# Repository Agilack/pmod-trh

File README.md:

PMOD Temperature and Humidity
=============================

This PMOD use an Si7021 sensor for temperature and humidity measurement.

**WARNING** Because of a bad choice into io assignment, it is not possible to
use UART TX/RX pins on PMOD connector (conflict for SERCOM0 already used for
I2C interface). Fortunately the TX/RX signals of SERCOM1 can be connected to
the pins named CTS/RTS of PMOD. This is an hardware bug that will be fix on
next version.

CAD source
----------

This board has been designed using KiCad EDA (version 6). All sources files
(schematics, routing, ...) are available into the `prj-kicad` folder.

This project is OpenHardware. You can re-use this design under terms of the
Creative Commons  ShareAlike license (CC-by-SA). See [LICENSE.md](LICENSE.md).

<table>
<tr>
<td></td>
<td></td>
</tr>
<tr>
<td>Fig1: Preview of the KiCad schematics (rev2)</td>
<td>Fig2: Preview of the KiCad routing (rev2)</td>
</tr>
</table>

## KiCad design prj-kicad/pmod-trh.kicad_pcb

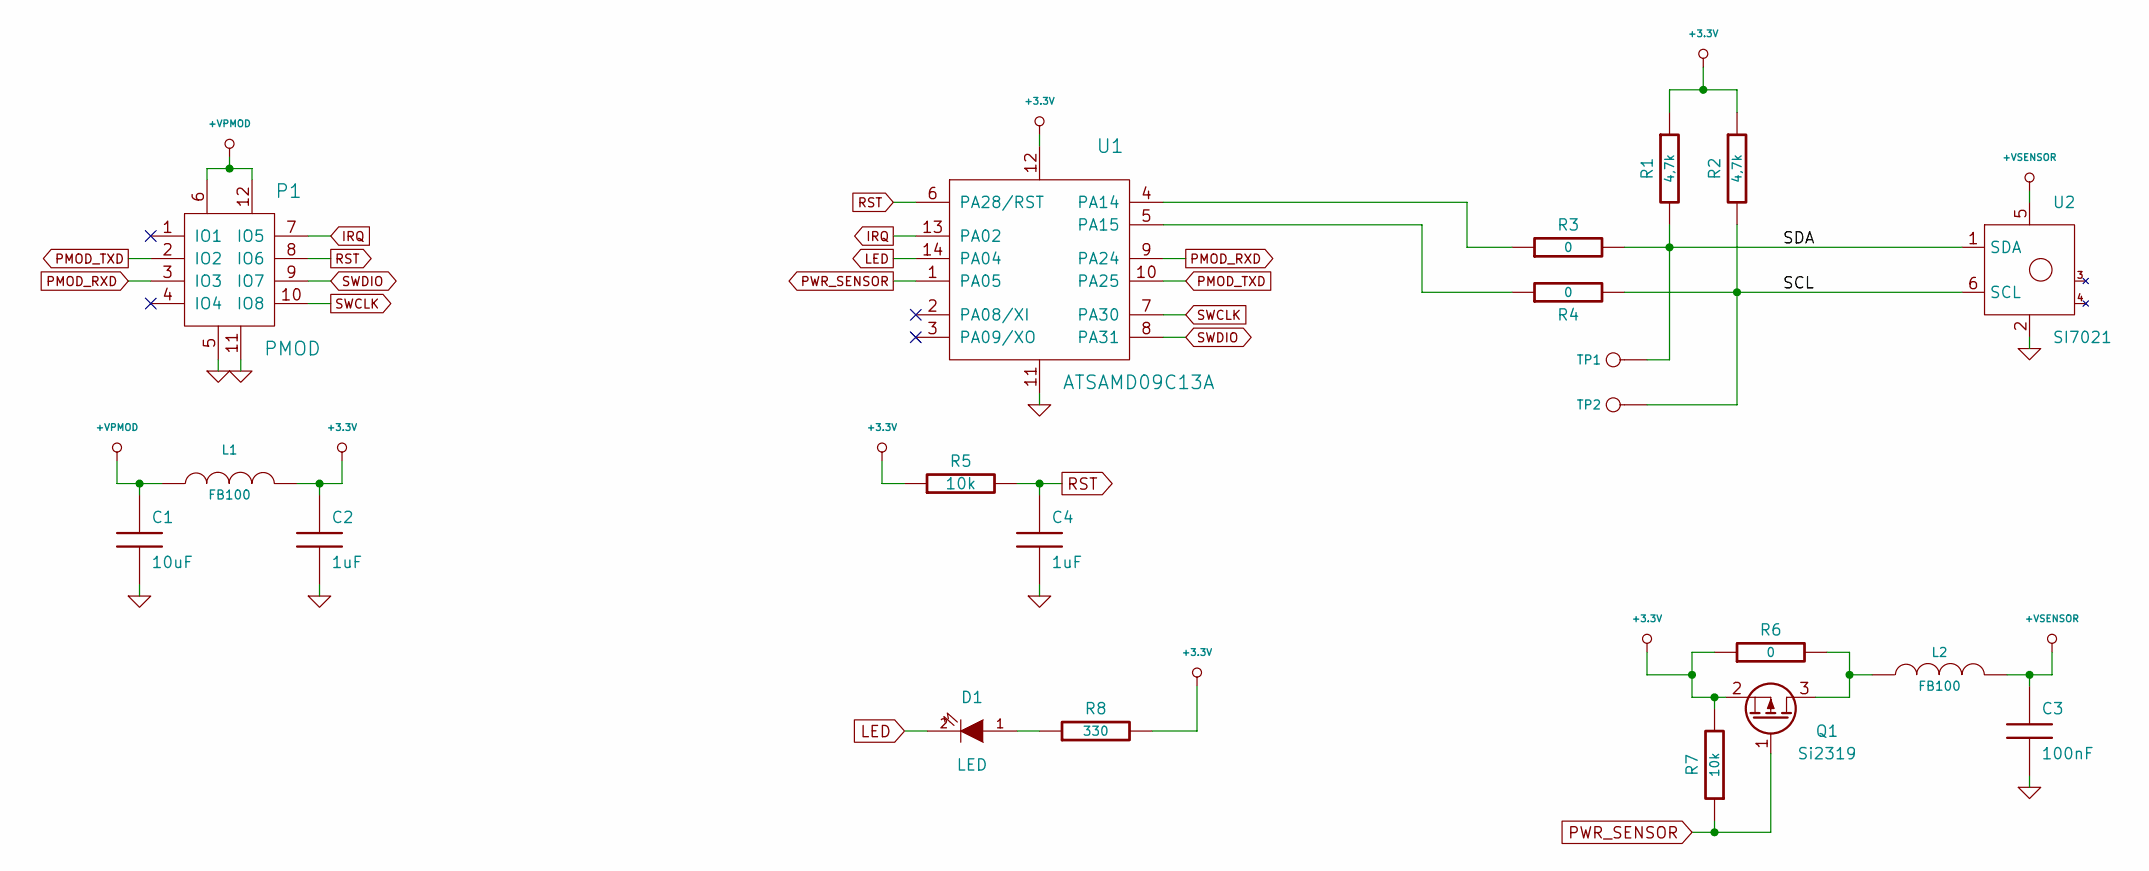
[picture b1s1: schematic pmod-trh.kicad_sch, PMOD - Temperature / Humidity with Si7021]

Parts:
C1: 10uF; SMD0805
C2, C4: 1uF; SMD0603
C3: 100nF; SMD0603
D1: LED; SMD0805
L1, L2: FB100; SMD0603
P1: PMOD; CONN_PMOD-Male
Q1: Si2319; SOT23-3
R1, R2: 4,7k; SMD0603
R3, R4, R6: 0; SMD0603
R5, R7: 10k; SMD0603
R8: 330; SMD0603
TP1, TP2: CONN_1; TP_SMD
U1: ATSAMD09C13A; SOIC-14
U2: SI7021; DFN6

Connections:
+3.3V: C2.1, L1.2, Q1.2 (S), R1.1, R2.1, R5.1, R6.1, R7.2, R8.2, U1.12
+VPMOD: C1.1, L1.1, P1.6, P1.12
+VSENSOR: C3.1, L2.2, U2.5
/SCL: R2.2, R4.2, TP2.1, U2.6 (SCL)
/SDA: R1.2, R3.2, TP1.1, U2.1 (SDA)
GND: C1.2, C2.2, C3.2, C4.2, P1.5, P1.11, U1.11, U2.2
IRQ: P1.7 (IO5), U1.13 (PA02)
LED: D1.2 (K), U1.14 (PA04)
unnamed: L2.1, Q1.3 (D), R6.2
unnamed: R3.1, U1.4 (PA14)
unnamed: R4.1, U1.5 (PA15)
unnamed: D1.1 (A), R8.1
PMOD_RXD: P1.3 (IO3), U1.9 (PA24)
PMOD_TXD: P1.2 (IO2), U1.10 (PA25)
PWR_SENSOR: Q1.1 (G), R7.1, U1.1 (PA05)
RST: C4.1, P1.8 (IO6), R5.2, U1.6 (PA28/RST)
SWCLK: P1.10 (IO8), U1.7 (PA30)
SWDIO: P1.9 (IO7), U1.8 (PA31)

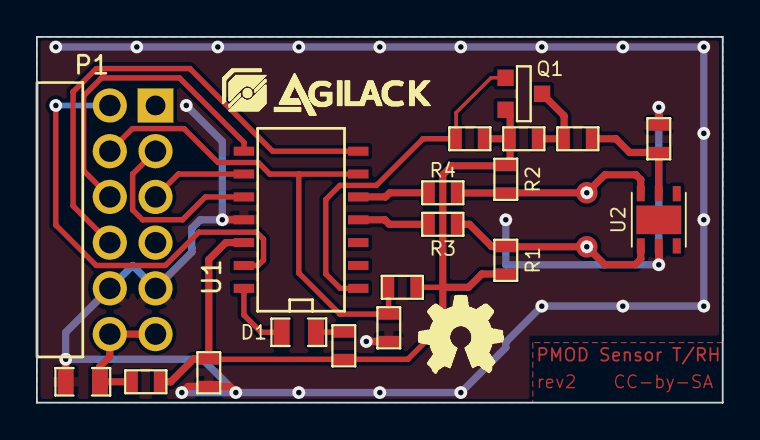
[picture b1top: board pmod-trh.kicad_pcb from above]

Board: 2 copper layers, 38.1 x 20.3 mm, 23 parts (0 on the bottom side), 18 nets.

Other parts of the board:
agilack-11.5: 450px; logo-agilack-11.5
logo_ohw: VAL**; logo-ohw

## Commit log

2022-07-14 --=={ Create Project }==--
    - Insert schematics and routing
2022-07-15 = ADD: Create production files for rev1
2022-07-21 = UPD: Insert picture of the first PCB \o/ ; update readme
2022-07-25 Firmware: Create a squeleton of firmware for the embedded ATSAMD mcu
2022-07-26 Firmware: Insert function to read temp and humidity from TRH7021 (work but a bit dirty)
2022-07-27 Firmware: Improve and cleanup Si7021 functions
2022-08-13 Hardware: Create rev2, fix known problems of rev1 (UART, reset) and add power control
2022-08-14 Hardware: Create production files for rev2
